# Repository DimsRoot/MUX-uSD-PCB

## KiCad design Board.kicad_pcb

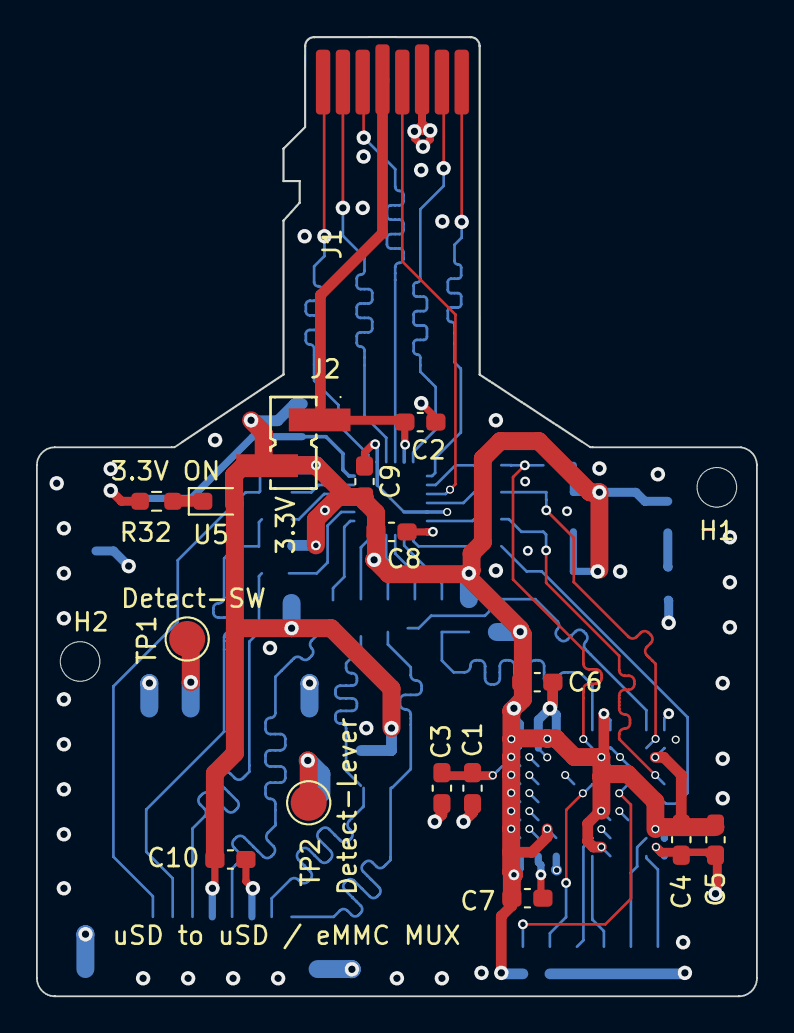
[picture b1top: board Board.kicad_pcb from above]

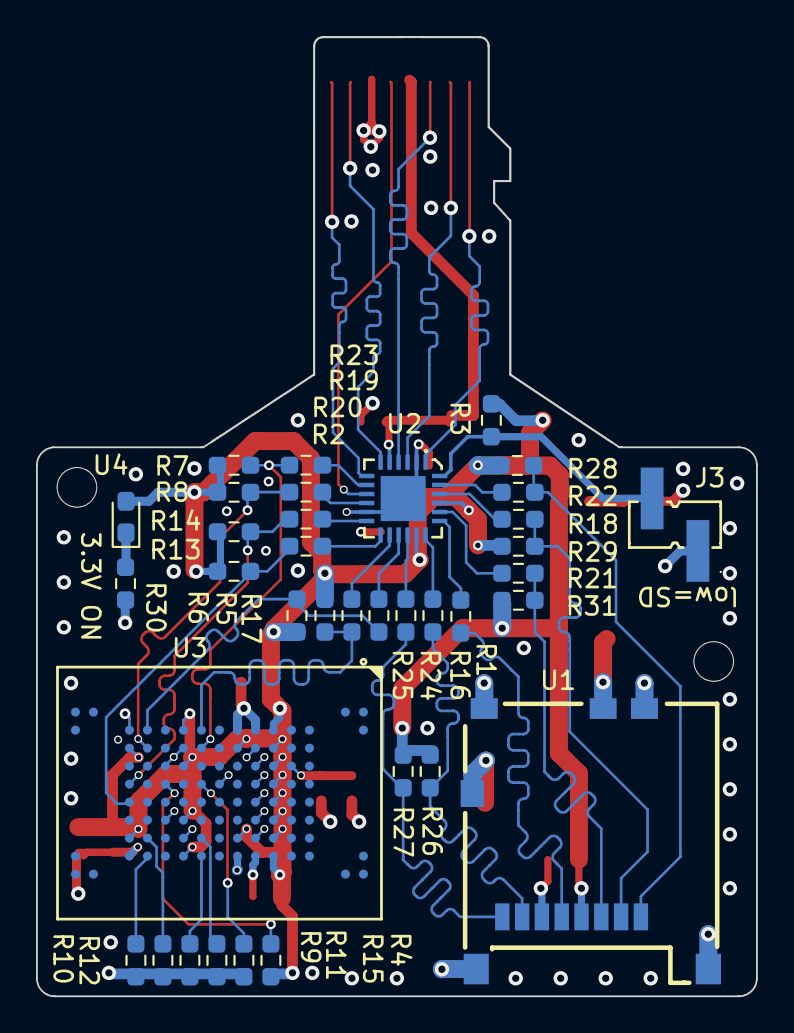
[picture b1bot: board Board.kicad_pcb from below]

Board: 4 copper layers, 40.0 x 53.3 mm, 54 parts (36 on the bottom side), 45 nets.

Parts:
C1, C2, C4, C6, C8, C9: CC0603KRX7R9BB104; C_0603_1608Metric_Pad1.08x0.95mm_HandSolder
C3, C5, C7, C10: CC0603MRX7R5BB475; C_0603_1608Metric_Pad1.08x0.95mm_HandSolder
H1, H2: MountingHole; MountingHole_2.2mm_M2
J1: uSD-Card-PAD; uSD-CARD-PAD-wOutline
J2, J3: TSM-102-01-L-SV; CONN-SMD_TSM-102-01-L-SV
R1, R2: RC0603FR-0722R1L; R_0603_1608Metric_Pad0.98x0.95mm_HandSolder
R3, R4, R13, R14: RC0603FR-074K75L; R_0603_1608Metric_Pad0.98x0.95mm_HandSolder
R5, R6, R7, R8, R9, R10, R11, R12, R15, R26, R27, R28, R29, R31: RC0603JR-0710KL; R_0603_1608Metric_Pad0.98x0.95mm_HandSolder
R16, R17, R18, R19, R20, R21, R22, R23, R24, R25: RC0603JR-070RL; R_0603_1608Metric_Pad0.98x0.95mm_HandSolder
R30, R32: RC0603JR-071KL; R_0603_1608Metric_Pad0.98x0.95mm_HandSolder
TP1, TP2: TestPoint; TestPoint_Pad_D2.0mm
U1: 5025700893; TF-SMD_5025700893
U2: TXS02612RTWR; WQFN-24_L4.0-W4.0-P0.50-TL-EP2.5
U3: MTFC32GAPALNA-AIT; TBGA-100_L18.0-W14.0-P1.00-TL_MTFC32GAPALNA-AIT
U4, U5: 19-213/GHC-YR2U1/3T; LED_0603_1608Metric_Pad1.05x0.95mm_HandSolder

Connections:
/MUX_SEL: J3.2, R3.1, U2.24 (SEL)
/PAD_uSD_CMD: J1.3 (CMD/SDI), U2.4 (CMDA)
/PAD_uSD_DAT0: J1.7 (DAT0/SDO), U2.6 (DAT0A)
/PAD_uSD_DAT1: J1.8 (DAT1/NC), U2.7 (DAT1A)
/PAD_uSD_DAT2: J1.1 (DAT2/NC), U2.1 (DAT2A)
/PAD_uSD_DAT3: J1.2 (DAT3/CS), U2.3 (DAT3A)
/PAD_uSD_SCLK: J1.5 (CLK/SCLK), U2.9 (CLKA)
/SDCARD_CLK: R1.2, U1.5 (CLK)
/SDCARD_CLK_R: R1.1, U2.19 (CLKB0)
/SDCARD_CMD: R21.2, R31.1, U1.3 (CMD)
/SDCARD_CMD_R: R21.1, U2.20 (CMDB0)
/SDCARD_D0: R16.2, R26.1, U1.7 (DAT0)
/SDCARD_D0_R: R16.1, U2.18 (DAT0B0)
/SDCARD_D1: R24.2, R27.1, U1.8 (DAT1)
/SDCARD_D1_R: R24.1, U2.16 (DAT1B0)
/SDCARD_D2: R22.2, R28.1, U1.1 (DAT2)
/SDCARD_D2_R: R22.1, U2.23 (DAT2B0)
/SDCARD_D3: R18.2, R29.1, U1.2 (CD/DAT3)
/SDCARD_D3_R: R18.1, U2.22 (DAT3B0)
/eMMC_CLK: R2.2, R13.1, U3.P6 (CLK)
/eMMC_CLK_R: R2.1, U2.13 (CLKB1)
/eMMC_CMD: R14.1, R20.2, U3.P5 (CMD)
/eMMC_CMD_R: R20.1, U2.12 (CMDB1)
/eMMC_D0: R5.1, R17.2, U3.K2 (DAT0)
/eMMC_D0_R: R17.1, U2.14 (DAT0B1)
/eMMC_D1: R6.1, R25.2, U3.N2 (DAT1)
/eMMC_D1_R: R25.1, U2.15 (DAT1B1)
/eMMC_D2: R7.1, R23.2, U3.K3 (DAT2)
/eMMC_D2_R: R23.1, U2.8 (DAT2B1)
/eMMC_D3: R8.1, R19.2, U3.N3 (DAT3)
/eMMC_D3_R: R19.1, U2.10 (DAT3B1)
/eMMC_D4: R12.2, U3.N8 (DAT4)
/eMMC_D5: R11.2, U3.K8 (DAT5)
/eMMC_D6: R10.2, U3.N9 (DAT6)
/eMMC_D7: R9.2, U3.K9 (DAT7)
/eMMC_RST_N: R4.1, U3.M5 (RST_n)
GND: C1.1, C2.1, C3.2, C4.1, C5.2, C6.1, C7.2, C8.1, C9.1, C10.1, J1.6 (GND), J3.1, R9.1, R10.1, R11.1, R12.1, R15.1, R30.2, R32.2, U1.6 (VSS), U1.9 (Shell_Mount), U2.2 (GND), U2.11 (GND), U2.25 (EP), U3.G2 (VSS), U3.G3 (VSS), U3.G4 (VSS), U3.G5 (VSS), U3.G6 (VSS), U3.G7 (VSS), U3.G8 (VSS), U3.G9 (VSS), U3.H2 (VSSQ), U3.H9 (VSSQ), U3.J5 (VSS), U3.L3 (VSSQ), U3.L8 (VSSQ), U3.M4 (VSSQ), U3.M7 (VSSQ), U3.P2 (VSSQ), U3.P9 (VSSQ)
unnamed: TP1.1, U1.10 (DETECT-SW)
unnamed: TP2.1, U1.11 (DETECT_LEVER)
unnamed: R15.2, U3.K5 (DS)
unnamed: C1.2, C3.1, U3.E4 (VDDIM)
unnamed: R30.1, U4.1 (K)
unnamed: R32.1, U5.1 (K)
P3V3: C4.2, C5.1, C6.2, C7.1, C8.2, C9.2, C10.2, J2.2, R3.2, R4.2, R5.2, R6.2, R7.2, R8.2, R13.2, R14.2, R26.2, R27.2, R28.2, R29.2, R31.2, U1.4 (VDD), U2.17 (VCCB1), U2.21 (VCCB0), U3.F2 (VCC), U3.F3 (VCC), U3.F4 (VCC), U3.F5 (VCC), U3.F6 (VCC), U3.F7 (VCC), U3.F8 (VCC), U3.F9 (VCC), U3.H3 (VCCQ), U3.H8 (VCCQ), U3.L2 (VCCQ), U3.L4 (VCCQ), U3.L7 (VCCQ), U3.L9 (VCCQ), U3.P3 (VCCQ), U3.P8 (VCCQ), U4.2 (A), U5.2 (A)
P3V3_SD: C2.2, J1.4 (VDD), J2.1, U2.5 (VCCA)

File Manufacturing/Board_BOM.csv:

"Id";"Designator";"Footprint";"Quantity";"Designation";"Supplier and ref";
1;"C5,C3,C10,C7";"C_0603_1608Metric_Pad1.08x0.95mm_HandSolder";4;"CC0603MRX7R5BB475";;;
2;"C8,C2,C1,C9,C4,C6";"C_0603_1608Metric_Pad1.08x0.95mm_HandSolder";6;"CC0603KRX7R9BB104";;;
3;"J2,J3";"CONN-SMD_TSM-102-01-L-SV";2;"TSM-102-01-L-SV";;;
4;"U5,U4";"LED_0603_1608Metric_Pad1.05x0.95mm_HandSolder";2;"19-213/GHC-YR2U1/3T";;;
5;"R32,R30";"R_0603_1608Metric_Pad0.98x0.95mm_HandSolder";2;"RC0603JR-071KL";;;
6;"R26,R10,R9,R7,R5,R6,R15,R31,R29,R27,R12,R8,R28,R11";"R_0603_1608Metric_Pad0.98x0.95mm_HandSolder";14;"RC0603JR-0710KL";;;
7;"R3,R4,R14,R13";"R_0603_1608Metric_Pad0.98x0.95mm_HandSolder";4;"RC0603FR-074K75L";;;
8;"U1";"TF-SMD_5025700893";1;"5025700893";;;
9;"R18,R19,R22,R23,R17,R21,R24,R16,R20,R25";"R_0603_1608Metric_Pad0.98x0.95mm_HandSolder";10;"RC0603JR-070RL";;;
10;"R2,R1";"R_0603_1608Metric_Pad0.98x0.95mm_HandSolder";2;"RC0603FR-0722R1L";;;
11;"U3";"TBGA-100_L18.0-W14.0-P1.00-TL_MTFC32GAPALNA-AIT";1;"MTFC32GAPALNA-AIT";;;
12;"U2";"WQFN-24_L4.0-W4.0-P0.50-TL-EP2.5";1;"TXS02612RTWR";;;

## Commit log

2025-06-22 Initial version of the uSD-eMMC-Mux board
2025-06-22 Add pdf
2025-06-23 update via drilling size and prod files
